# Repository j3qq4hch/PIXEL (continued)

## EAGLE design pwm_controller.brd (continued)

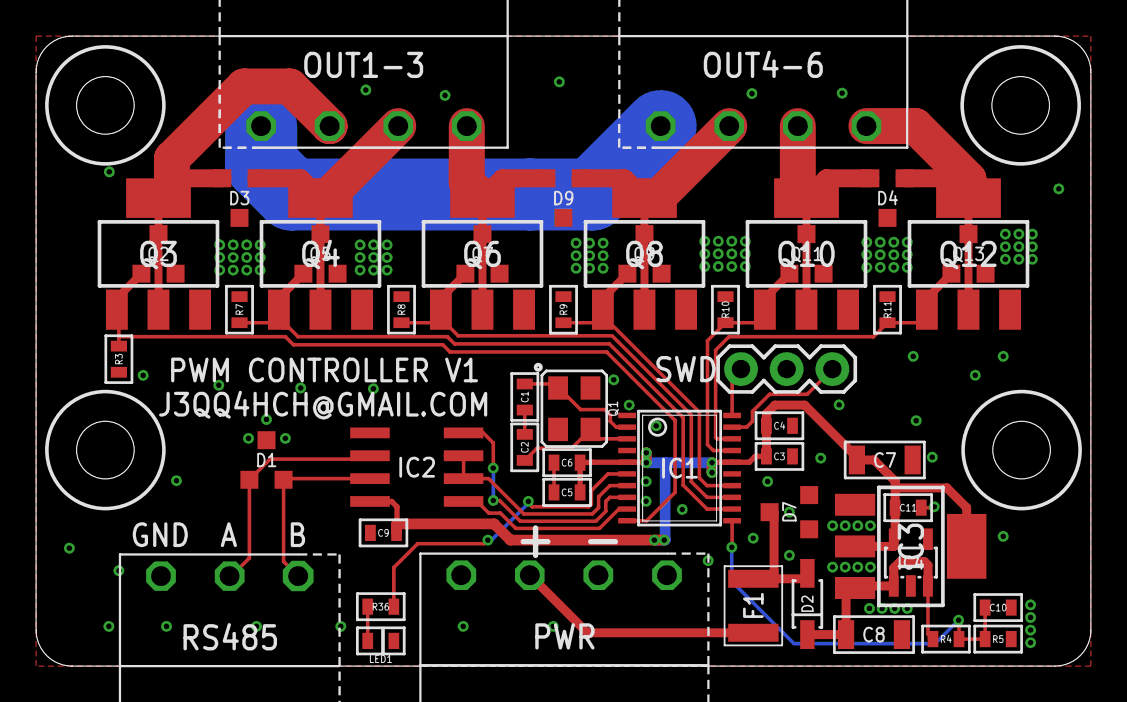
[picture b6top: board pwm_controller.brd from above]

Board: 2 copper layers, 58.6 x 35.0 mm, 51 parts (0 on the bottom side), 29 nets.

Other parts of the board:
U$1: BOARD_OUTLINE_V4

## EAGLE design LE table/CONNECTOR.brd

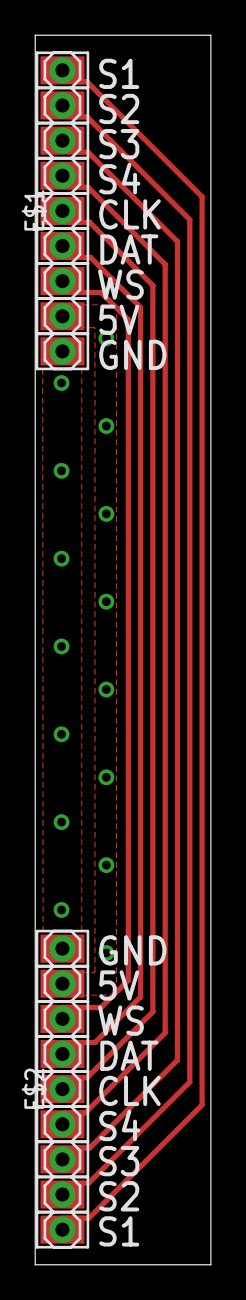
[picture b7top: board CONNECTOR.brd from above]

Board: 2 copper layers, 10.0 x 70.0 mm, 4 parts (0 on the bottom side), 9 nets.

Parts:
CON1, CON3: CONNECTOR
E$1, E$2: 1X09-PTH_2

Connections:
unnamed: CON1.1, CON3.9, E$1.1, E$2.9
unnamed: CON1.2, CON3.8, E$1.2, E$2.8
unnamed: CON1.3, CON3.7
unnamed: CON1.4, CON3.6
unnamed: CON1.5, CON3.5
unnamed: CON1.6, CON3.4
unnamed: CON1.7, CON3.3
unnamed: CON1.8, CON3.2
unnamed: CON1.9, CON3.1

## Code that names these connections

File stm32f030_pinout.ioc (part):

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Mcu.Name=STM32F030K6Tx
Mcu.Package=LQFP32
Mcu.UserName=STM32F030K6Tx
PA0.Mode=IN0
PA0.Signal=ADC_IN0
PA1.Mode=Hardware Flow Control (RS485)
PA1.Signal=USART1_DE
PA10.Signal=S_TIM1_CH3
PA13.Mode=Serial_Wire
PA13.Signal=SYS_SWDIO
PA14.Mode=Serial_Wire
PA14.Signal=SYS_SWCLK
PA2.Mode=Asynchronous
PA2.Signal=USART1_TX
PA3.Mode=Asynchronous
PA3.Signal=USART1_RX
PA4.Mode=IN4
PA4.Signal=ADC_IN4
PA5.Mode=IN5
PA5.Signal=ADC_IN5
PA6.Mode=IN6
PA6.Signal=ADC_IN6
PA8.Signal=S_TIM1_CH1
PA9.Signal=S_TIM1_CH2
PB3.Mode=Simplex_Bidirectional_Master
PB3.Signal=SPI1_SCK
PB5.Mode=Simplex_Bidirectional_Master
PB5.Signal=SPI1_MOSI
PF0-OSC_IN.Mode=HSE-External-Oscillator
PF0-OSC_IN.Signal=RCC_OSC_IN
PF1-OSC_OUT.Mode=HSE-External-Oscillator
PF1-OSC_OUT.Signal=RCC_OSC_OUT

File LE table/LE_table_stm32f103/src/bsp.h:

#include "stm32f10x.h"

#define LED_Pin                GPIO_Pin_13
#define LED_GPIO_Port          GPIOC

#define TABLE_CLK_Port          GPIOB
#define TABLE_CLK_Pin           GPIO_Pin_10

#define TABLE_DATA_Port          GPIOB
#define TABLE_DATA_Pin           GPIO_Pin_1

#define TABLE_CLK_TICK()        (GPIO_SetBits(TABLE_CLK_Port, TABLE_CLK_Pin), GPIO_ResetBits(TABLE_CLK_Port, TABLE_CLK_Pin))

#define DBG_UART                USART1
#define DBG_TX_Pin              GPIO_Pin_9
#define DBG_TX_GPIO_Port        GPIOA

#define DBG_RX_Pin              GPIO_Pin_10
#define DBG_RX_GPIO_Port        GPIOA

#define SENS1_Pin       GPIO_Pin_4
#define SENS1_Port      GPIOA
//adc_in4


#define SENS2_Pin       GPIO_Pin_5
#define SENS2_Port      GPIOA
//adc_in5


#define SENS3_Pin       GPIO_Pin_6
#define SENS3_Port      GPIOA
//adc_in6


#define SENS4_Pin       GPIO_Pin_7
#define SENS4_Port      GPIOA
//adc_in7

void board_init(void);

static inline void GPIO_toggle(GPIO_TypeDef* GPIOx, uint16_t GPIO_Pin)
{
(GPIOx->ODR & GPIO_Pin) ? (GPIOx->BRR = GPIO_Pin) : (GPIOx->BSRR = GPIO_Pin);
}

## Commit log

2017-02-20 initial import
2017-02-20 blah
2017-02-20 SDR0604 Series inductor
2017-02-20 MC74VHC1GT125 and FDC6420C
2017-02-20 Minor fixes
2017-02-25 added STM32F030K6T6
2017-02-26 MCU replaced with STM32F030K6T6
2017-02-26 Oscilator library
2017-02-26 First step
2017-02-26 Diodes library
2017-02-26 Preliminary LED driver
2017-02-27 minor changes
2017-02-28 added PT4115 reference board
2017-02-28 naming fixes pixel8 initial import
2017-03-01 -added DC-DC
2017-03-01 Led driver schematics added
2017-03-01 SDR0805 series inductor added
2017-03-01 SOT-23 P and N chanel MOSFETs added
2017-03-01 LED driver updated
2017-03-02 pcb attmepts
2017-03-02 -blah
2017-03-04 pixelD added
2017-03-04 First attempts in routing the PCB
2017-03-05 First attempts in routing
2017-03-06 LED Driver
2017-03-07 All devices have been imported to the libraries
2017-03-07 Routing
2017-03-11 PCB finalization
2017-03-12 pixel8 update
2017-03-12 pixelD update
2017-03-12 some tmp files added
2017-03-12 cleanup
2017-03-12 RTU preliminary frames
2017-03-12 RTU logo on silkscreen
2017-03-12 PCB Finalization #2
2017-03-13 32 ver 3dview added
2017-03-13 -pixel32 update
2017-03-14 -more edge connectors
2017-03-15 update and cleanup
2017-03-15 voltage regulator recalculated, minor fixes, attributes
2017-03-15 input sense divider values added boot0 fix
2017-03-15 TME part numbers added
2017-03-15 added reset pad
2017-03-15 Reset pad routing, clearance error resolving
2017-03-16 Preliminary BOM
2017-03-16 -pixel 3d model update
2017-03-16 minor updates
2017-03-17 Added spare power connector just in case. New 3d view.
2017-03-17 RTU logo removed
2017-03-17 Moustashe added
2017-03-17 naming fixes minor silk fixes
2017-03-17 -directories reorganisation added gerbers for moustache board
2017-03-17 PCB Stencil added
2017-04-03 BOM update
2017-04-22 Another Brick In the Wall initial import
2017-04-22 Le table initial import
2017-04-22 SW initial import
2017-05-02 -LE TABLE completed
2017-06-13 Software import
